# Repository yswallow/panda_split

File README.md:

# パンダスルーホール
split 5x4 keyboard using MCP23017

## Parts (one hand)

| name | number | description | site | substitute |
| ---- | ---- | ---- | ---- | ---- |
| MJ-4PP-9 | 2 | TRRS jack | http://akizukidenshi.com/catalog/g/gC-06070/ | PJ-320A |
| LED| 1 |  |  |  |
| Resistor | 1 | for LED | http://akizukidenshi.com/catalog/g/gR-25472/ |  |
| Capacitor 0.1μF | 1 | 2.5mm pitch | http://akizukidenshi.com/catalog/g/gP-00090/ |  |
| Slide Switch | 2 | 2.54mm pitch, SPDT | http://akizukidenshi.com/catalog/g/gP-08790/ |  |
| MCP23017-E/SP | 2 | I2C I/O Expander | http://akizukidenshi.com/catalog/g/gI-09486/ |  |
| IC Socket | 2 | 28pin, 300mil | http://akizukidenshi.com/catalog/g/gP-00013/ |  |
| M3x10mm Screw | 4 |  |  |  |
| M3 nut | 4 |  |  |  |
| rubber feet | 4 | >4mm thick |  |  |
| Kailh Socket | 20 | choc or MX |  |  |
| Keyboard Switch | 20 | choc or MX |  |  |

and PCB, Top/Bottom Plate, panda-pendant, 2 trrs cable.

## Build log (not using top/bottom plate)
http://y-sni.hatenablog.com/entry/2019/03/08/170233

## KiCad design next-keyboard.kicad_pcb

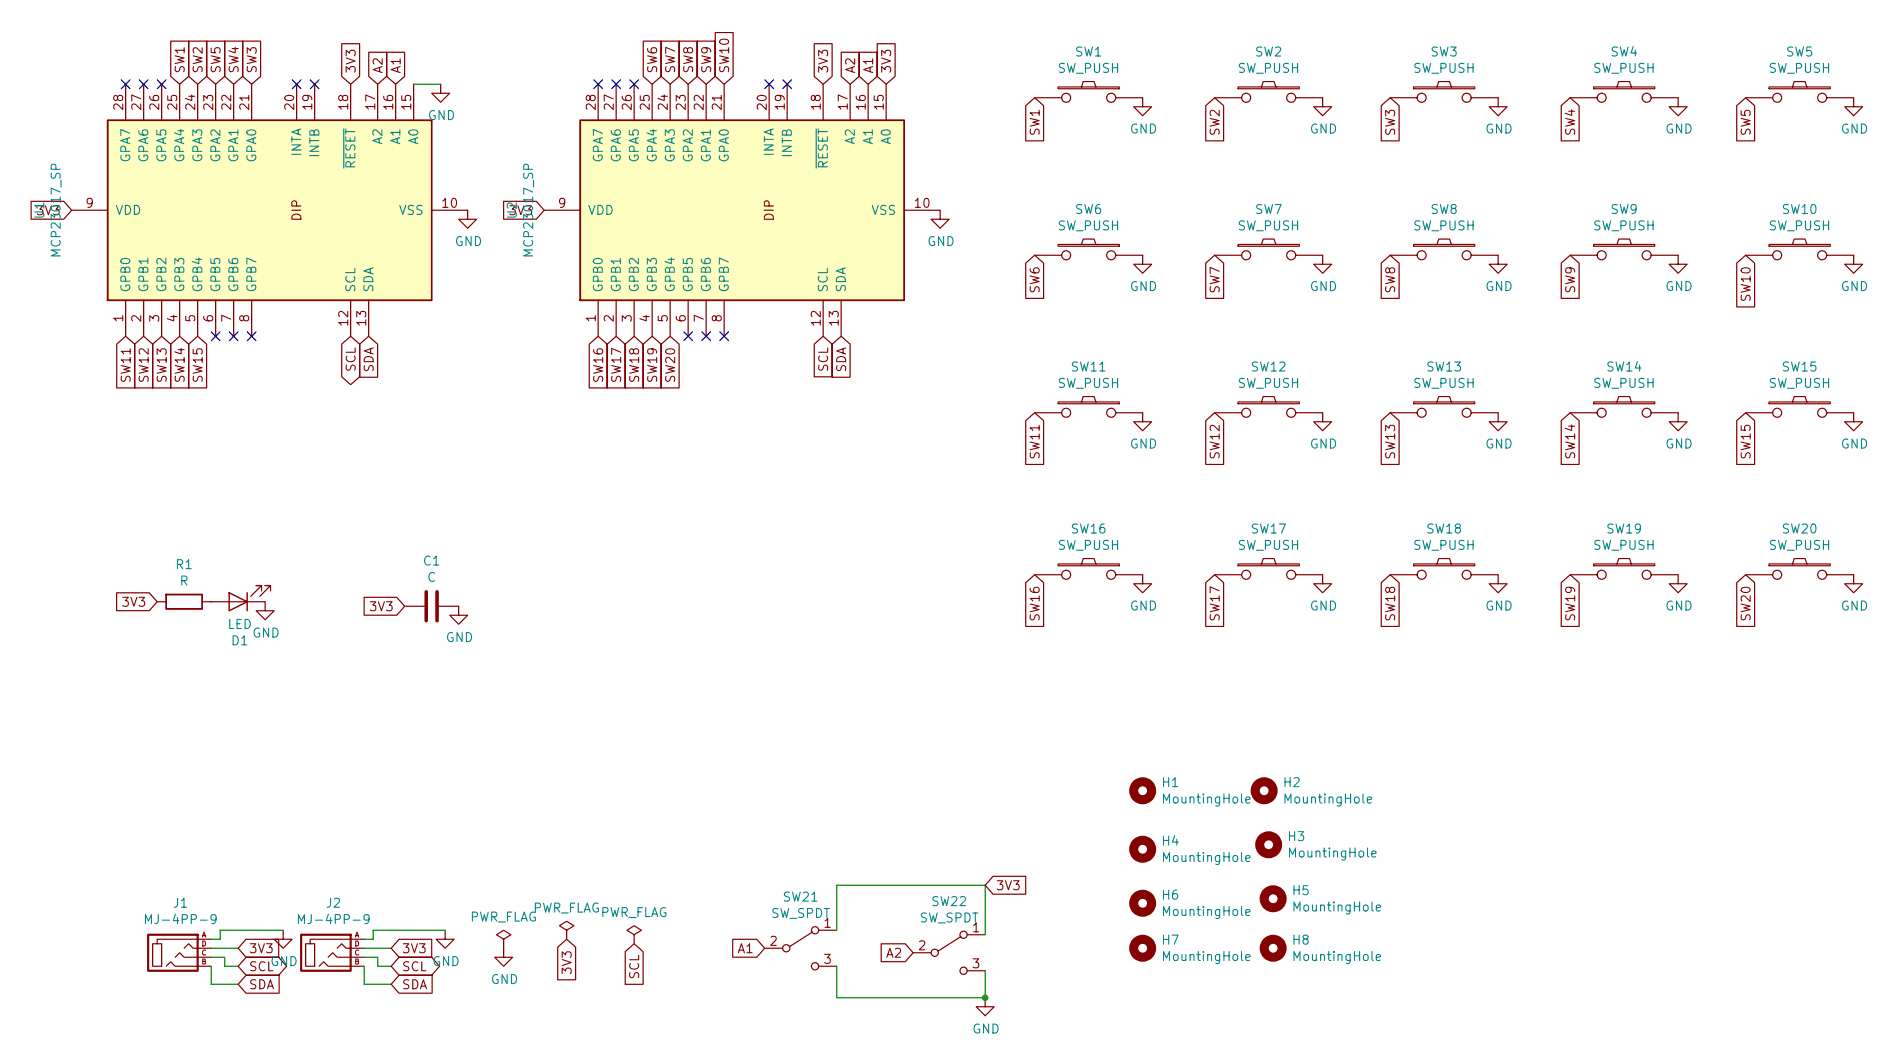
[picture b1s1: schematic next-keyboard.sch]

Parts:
C1: C; C_Disc_D3.8mm_W2.6mm_P2.50mm
D1: LED; LED_D3.0mm
H1, H2, H3, H4: MountingHole; MountingHole_3.2mm_M3
H5, H6, H7, H8: MountingHole; HOLE
J1, J2: MJ-4PP-9
R1: R; R_Axial_DIN0207_L6.3mm_D2.5mm_P7.62mm_Horizontal
SW1, SW2, SW3, SW4, SW5, SW6, SW7, SW8, SW9, SW10, SW11, SW12, SW13, SW14, SW15, SW16, SW17, SW18, SW19, SW20: SW_PUSH; CherryMX_KailhLowProfile_Hotswap_singleside_5pin
SW21, SW22: SW_SPDT; SlideSwitch_SS-12D00
U1, U2: MCP23017_SP; DIP-28_W7.62mm_Socket

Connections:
3V3: C1.2, J1.D, J2.D, R1.2, SW21.1 (A), SW22.1 (A), U1.9 (VDD), U1.18 (~RESET~), U2.9 (VDD), U2.15 (A0), U2.18 (~RESET~)
A1: SW21.2 (B), U1.16 (A1), U2.16 (A1)
A2: SW22.2 (B), U1.17 (A2), U2.17 (A2)
GND: C1.1, D1.1 (K), J1.A, J2.A, SW1.1, SW2.2, SW3.2, SW4.2, SW5.2, SW6.1, SW7.2, SW8.2, SW9.2, SW10.2, SW11.1, SW12.2, SW13.2, SW14.2, SW15.2, SW16.1, SW17.2, SW18.2, SW19.2, SW20.2, SW21.3 (C), SW22.3 (C), U1.10 (VSS), U1.15 (A0), U2.10 (VSS)
unnamed: D1.2 (A), R1.1
SCL: J1.C, J2.C, U1.12 (SCL), U2.12 (SCL)
SDA: J1.B, J2.B, U1.13 (SDA), U2.13 (SDA)
SW1: SW1.2, U1.25 (GPA4)
SW2: SW2.1, U1.24 (GPA3)
SW3: SW3.1, U1.21 (GPA0)
SW4: SW4.1, U1.22 (GPA1)
SW5: SW5.1, U1.23 (GPA2)
SW6: SW6.2, U2.25 (GPA4)
SW7: SW7.1, U2.24 (GPA3)
SW8: SW8.1, U2.23 (GPA2)
SW9: SW9.1, U2.22 (GPA1)
SW10: SW10.1, U2.21 (GPA0)
SW11: SW11.2, U1.1 (GPB0)
SW12: SW12.1, U1.2 (GPB1)
SW13: SW13.1, U1.3 (GPB2)
SW14: SW14.1, U1.4 (GPB3)
SW15: SW15.1, U1.5 (GPB4)
SW16: SW16.2, U2.1 (GPB0)
SW17: SW17.1, U2.2 (GPB1)
SW18: SW18.1, U2.3 (GPB2)
SW19: SW19.1, U2.4 (GPB3)
SW20: SW20.1, U2.5 (GPB4)

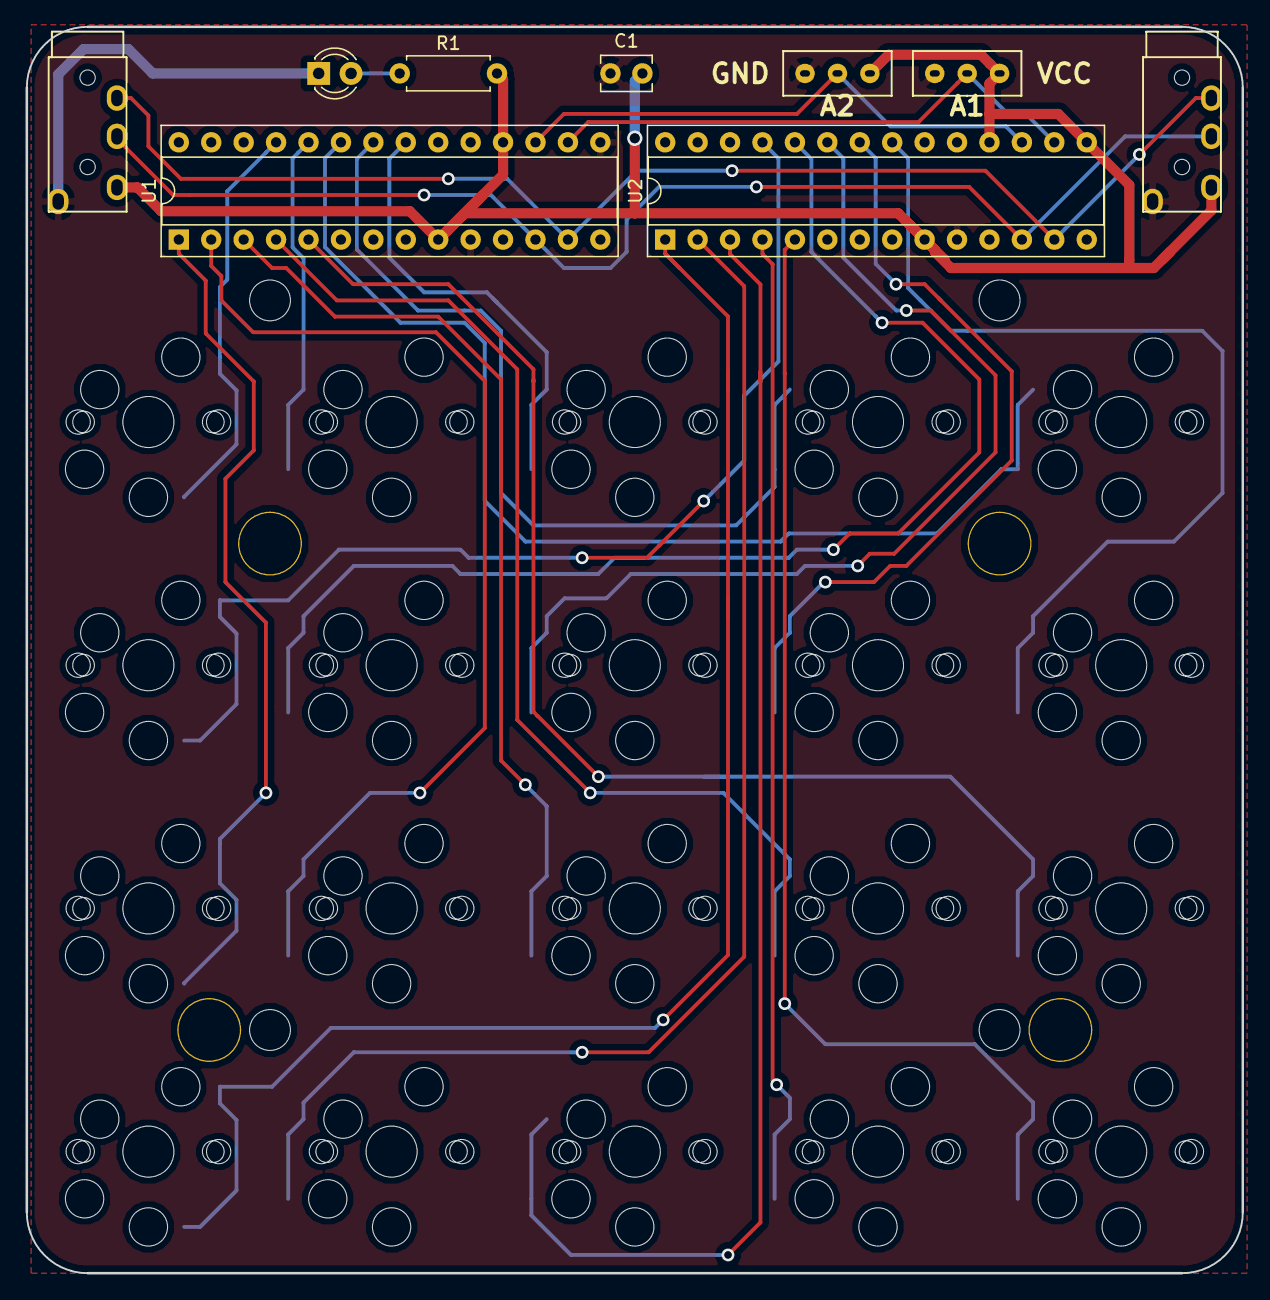
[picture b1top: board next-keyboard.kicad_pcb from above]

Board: 2 copper layers, 95.2 x 97.6 mm, 37 parts (0 on the bottom side), 27 nets.

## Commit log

2019-02-13 init
2019-06-18 produce
2019-07-08 add all data
2019-09-23 fix typos
